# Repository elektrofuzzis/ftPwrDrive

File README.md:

# ftPwrDrive
The ftPwrDrive is a i²c based stepper motor driver for fischertechnik, Arduino &amp; Raspberry. The project contains the stepper motor drivers hardware, the firmware and interface libraries to use the hardware with multiple plattforms.

Please checkout the <a href="https://github.com/elektrofuzzis/ftPwrDrive/wiki">online manual</a>. Since the hardware is a complex smd pcb, you could buy a plug&play device at <a href="https://gundermann-software.de/shop/">gundermann.org</a>.

To check out the latest releases please follow up the <a href="https://github.com/elektrofuzzis/ftPwrDrive/wiki/Changelog">version history</a>.

<hr width="100%" />

Der ftPwrDrive ist ein Schrittmotortreiber für fischertechnik, Arduino &amp; Raspberry auf i²C-Basis. Das Projekt beinhaltet sowohl doe Schrittmotortreiberhardware und die notwendige Firmware als auch Interface Bibliotheken für unterschiedliche Plattformen.

Bitte lesen Sie das <a href="https://github.com/elektrofuzzis/ftPwrDrive/wiki">Online Manual</a>. Die Hardware besteht aus einer komplexen, SMD-bestückten Platine. Sie können den ftPwrDrive auch als fertiges Gerät bei <a href="https://gundermann-software.de/shop/">gundermann.org</a> bestellen.

Das Changelog für die aktuelle Version finden sie<a href="https://github.com/elektrofuzzis/ftPwrDrive/wiki/Changelog"> hier</a>.

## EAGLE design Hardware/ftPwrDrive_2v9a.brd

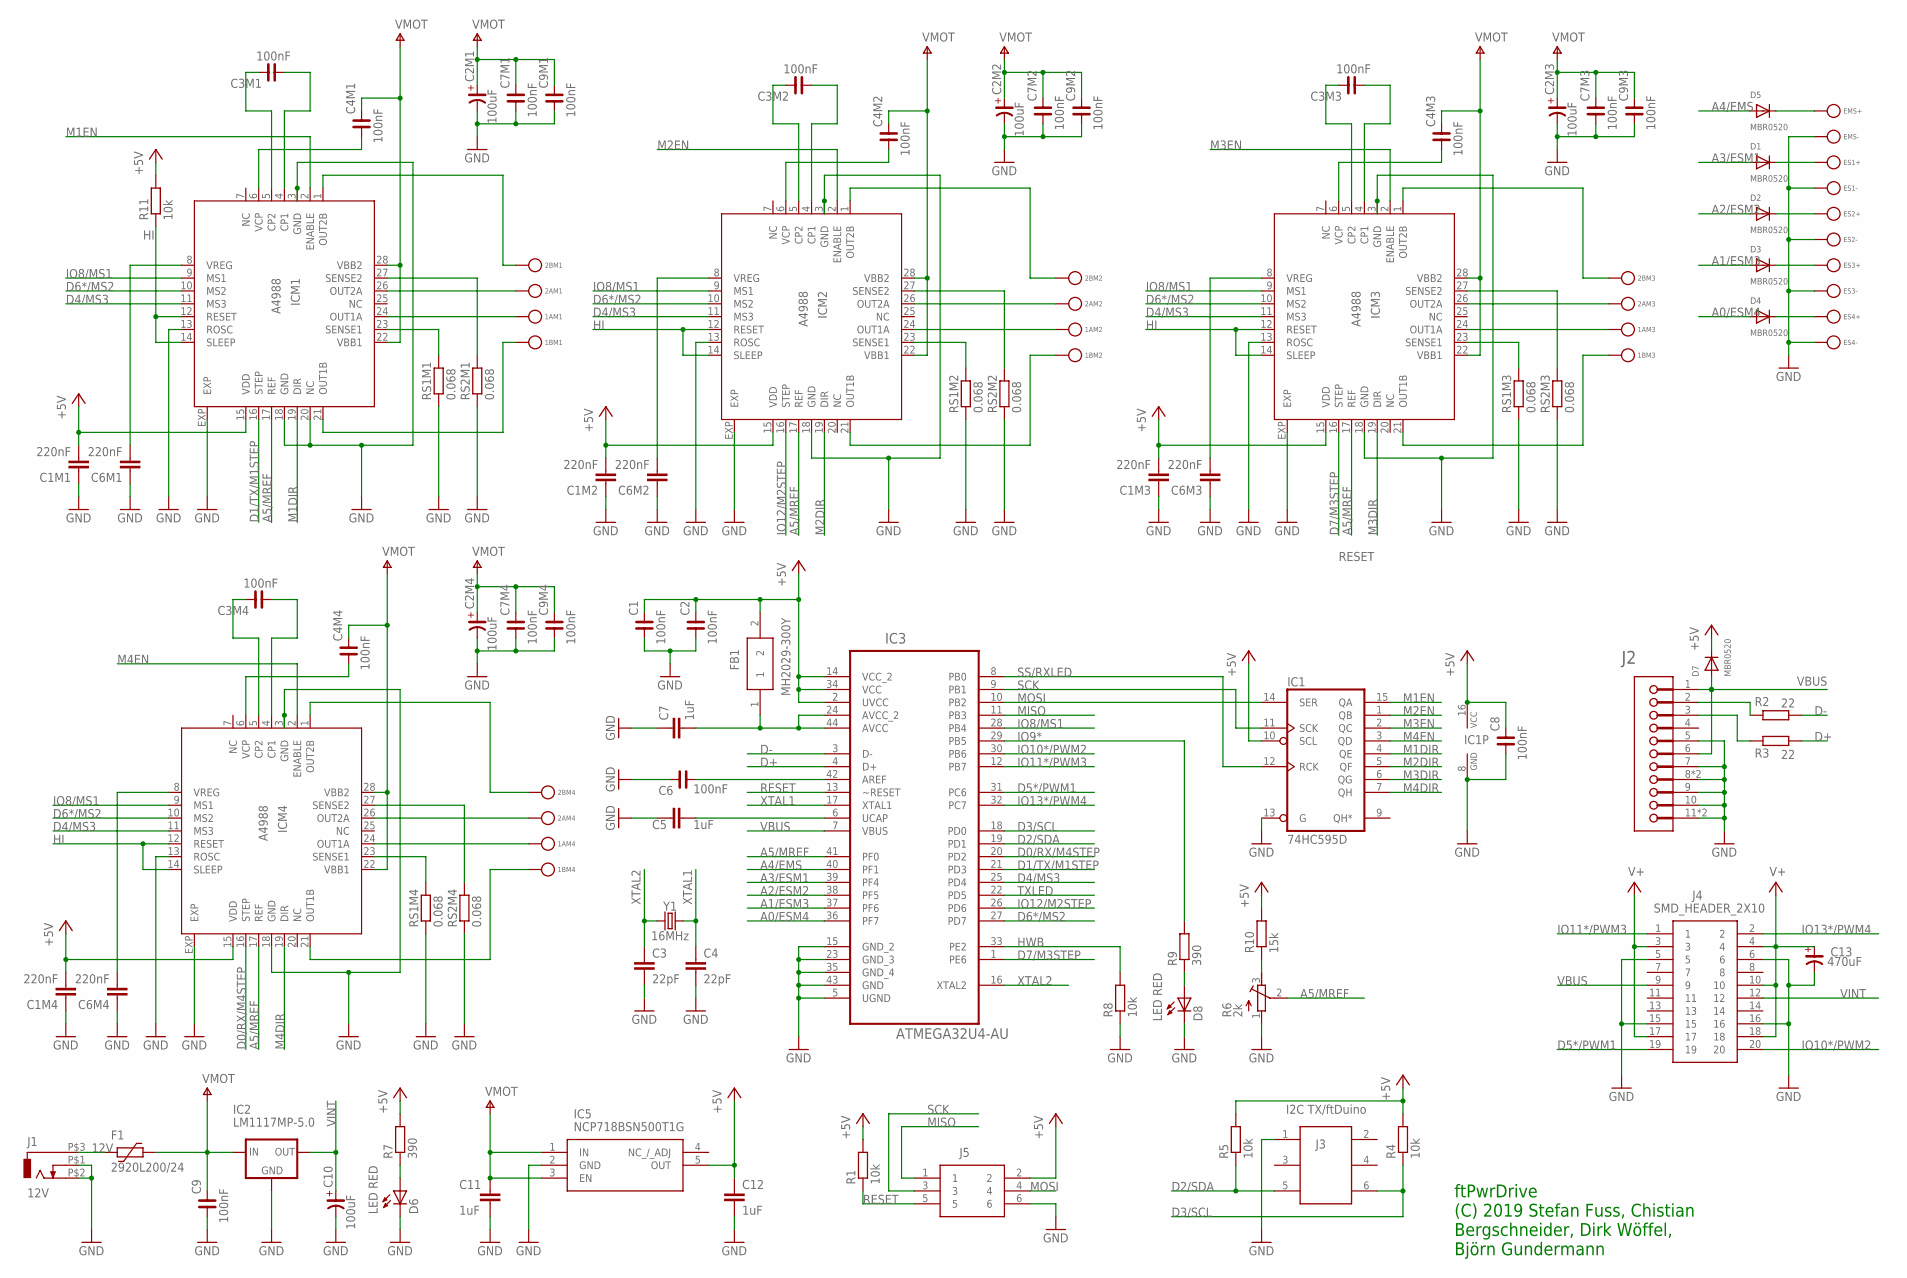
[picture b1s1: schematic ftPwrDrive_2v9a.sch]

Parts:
1AM1, 1AM2, 1AM3, 1AM4, 1BM1, 1BM2, 1BM3, 1BM4, 2AM1, 2AM2, 2AM3, 2AM4, 2BM1, 2BM2, 2BM3, 2BM4: BUNDHUELSE2; BUNDHUELSE
C1, C2, C3M1, C3M2, C3M3, C3M4, C4M1, C4M2, C4M3, C4M4, C6, C7M1, C7M2, C7M3, C7M4, C8, C9, C9M1, C9M2, C9M3, C9M4: 100nF; C0603
C1M1, C1M2, C1M3, C1M4, C6M1, C6M2, C6M3, C6M4: 220nF; C0603K
C2M1, C2M2, C2M3, C2M4, C10: 100uF; CSV-D
C3, C4: 22pF; C0603K
C5, C7, C11, C12: 1uF; C0603K
C13: 470uF; CSV-E/F
D1, D2, D3, D4, D5, D7: MBR0520; SOD-123
D6, D8: LED RED; CHIP-LED0805
EMS+: BUNDHUELSE2; BUNDHUELSE
EMS-: BUNDHUELSE2; BUNDHUELSE
ES1+, ES1-, ES2+, ES2-, ES3+, ES3-, ES4+, ES4-: BUNDHUELSE2; BUNDHUELSE
F1: 2920L200/24; 2920L
FB1: MH2029-300Y; BEADC2016X130N
IC1: 74HC595D; SO16
IC2: LM1117MP-5.0; SOT223
IC3: ATMEGA32U4-AU; QFP80P1200X1200X120-44N
IC5: NCP718BSN500T1G; SOT95P280X100-5N
ICM1, ICM2, ICM3, ICM4: A4988; QFN28ET
J1: 12V; RASM7X2
J2: AMPHENOL_10118194-0001LFAMPHENOL_10118194-0001LF_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; AMPHENOL_10118194-0001LF_0
J3: I2C TX/ftDuino; SMTHEADER06
J4: SMD_HEADER_2X10
J5: SMD_HEADER_2X03
R1, R4, R5, R8, R11: 10k; R0603
R2, R3: 22; R0603
R6: 2k; RTRIM4G/J
R7, R9: 390; R0603
R10: 15k; R0603
RS1M1, RS1M2, RS1M3, RS1M4, RS2M1, RS2M2, RS2M3, RS2M4: 0.068; R1206
Y1: 16MHz; HC49UP

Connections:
1AM1: 1AM1.P$1, ICM1.24 (OUT1A)
1AM2: 1AM2.P$1, ICM2.24 (OUT1A)
1AM3: 1AM3.P$1, ICM3.24 (OUT1A)
1AM4: 1AM4.P$1, ICM4.24 (OUT1A)
1BM1: 1BM1.P$1, ICM1.21 (OUT1B)
1BM2: 1BM2.P$1, ICM2.21 (OUT1B)
1BM3: 1BM3.P$1, ICM3.21 (OUT1B)
1BM4: 1BM4.P$1, ICM4.21 (OUT1B)
2AM1: 2AM1.P$1, ICM1.26 (OUT2A)
2AM2: 2AM2.P$1, ICM2.26 (OUT2A)
2AM3: 2AM3.P$1, ICM3.26 (OUT2A)
2AM4: 2AM4.P$1, ICM4.26 (OUT2A)
2BM1: 2BM1.P$1, ICM1.1 (OUT2B)
2BM2: 2BM2.P$1, ICM2.1 (OUT2B)
2BM3: 2BM3.P$1, ICM3.1 (OUT2B)
2BM4: 2BM4.P$1, ICM4.1 (OUT2B)
12V: F1.2, J1.P$3 (1)
+5V: C1.2, C1M1.2, C1M2.2, C1M3.2, C1M4.2, C2.2, C8.2, C12.1, D7.C, FB1.2, IC1.10 (SCL), IC1.16 (VCC), IC3.2 (UVCC), IC3.14 (VCC_2), IC3.34 (VCC), IC5.5 (OUT), ICM1.15 (VDD), ICM2.15 (VDD), ICM3.15 (VDD), ICM4.15 (VDD), J5.2, R1.2, R4.2, R5.2, R7.2, R10.2, R11.2
A0/ESM4: D4.A, IC3.36 (PF7)
A1/ESM3: D3.A, IC3.37 (PF6)
A2/ESM2: D2.A, IC3.38 (PF5)
A3/ESM1: D1.A, IC3.39 (PF4)
A4/EMS: D5.A, IC3.40 (PF1)
A5/MREF: IC3.41 (PF0), ICM1.17 (REF), ICM2.17 (REF), ICM3.17 (REF), ICM4.17 (REF), R6.2 (S)
D0/RX/M4STEP: IC3.20 (PD2), ICM4.16 (STEP)
D1/TX/M1STEP: IC3.21 (PD3), ICM1.16 (STEP)
D2/SDA: IC3.19 (PD1), J3.5, R5.1
D3/SCL: IC3.18 (PD0), J3.6, R4.1
D4/MS3: IC3.25 (PD4), ICM1.11 (MS3), ICM2.11 (MS3), ICM3.11 (MS3), ICM4.11 (MS3)
D5*/PWM1: IC3.31 (PC6), J4.19
D6*/MS2: IC3.27 (PD7), ICM1.10 (MS2), ICM2.10 (MS2), ICM3.10 (MS2), ICM4.10 (MS2)
D7/M3STEP: IC3.1 (PE6), ICM3.16 (STEP)
D+: IC3.4 (D+), R3.1
D-: IC3.3 (D-), R2.1
ES1+: D1.C, ES1+.P$1
ES1+1: D5.C, EMS+.P$1
ES2+: D2.C, ES2+.P$1
ES3+: D3.C, ES3+.P$1
ES4+: D4.C, ES4+.P$1
GND: C1.1, C1M1.1, C1M2.1, C1M3.1, C1M4.1, C2.1, C2M1.-, C2M2.-, C2M3.-, C2M4.-, C3.2, C4.2, C5.1, C6.1, C6M1.1, C6M2.1, C6M3.1, C6M4.1, C7.1, C7M1.1, C7M2.1, C7M3.1, C7M4.1, C8.1, C9.1, C9M1.1, C9M2.1, C9M3.1, C9M4.1, C10.-, C11.1, C12.2, C13.-, D6.C, D8.C, EMS-.P$1, ES1-.P$1, ES2-.P$1, ES3-.P$1, ES4-.P$1, IC1.8 (GND), IC1.13 (G), IC2.1 (GND), IC3.5 (UGND), IC3.15 (GND_2), IC3.23 (GND_3), IC3.35 (GND_4), IC3.43 (GND), IC5.2 (GND), ICM1.3 (GND), ICM1.13 (ROSC), ICM1.18 (GND), ICM1.20 (NC), ICM1.EXP, ICM2.3 (GND), ICM2.13 (ROSC), ICM2.18 (GND), ICM2.EXP, ICM3.3 (GND), ICM3.13 (ROSC), ICM3.18 (GND), ICM3.EXP, ICM4.3 (GND), ICM4.13 (ROSC), ICM4.18 (GND), ICM4.EXP, J1.P$1 (2), J1.P$2 (3), J2.5, J2.7 (MNT_2), J2.8 (MNT_3), J2.8-2 (MNT_3), J2.9 (MNT_4), J2.10 (MNT_5), J2.11 (MNT_6), J2.11-2 (MNT_6), J3.1, J4.5, J4.6, J4.15, J4.16, J5.6, R6.1 (A), R8.1, RS1M1.1, RS1M2.1, RS1M3.1, RS1M4.1, RS2M1.1, RS2M2.1, RS2M3.1, RS2M4.1
HI: ICM1.12 (RESET), ICM1.14 (SLEEP), ICM2.12 (RESET), ICM2.14 (SLEEP), ICM3.12 (RESET), ICM3.14 (SLEEP), ICM4.12 (RESET), ICM4.14 (SLEEP), R11.1
HWB: IC3.33 (PE2), R8.2
IO8/MS1: IC3.28 (PB4), ICM1.9 (MS1), ICM2.9 (MS1), ICM3.9 (MS1), ICM4.9 (MS1)
IO9*: IC3.29 (PB5), R9.2
IO10*/PWM2: IC3.30 (PB6), J4.20
IO11*/PWM3: IC3.12 (PB7), J4.1
IO12/M2STEP: IC3.26 (PD6), ICM2.16 (STEP)
IO13*/PWM4: IC3.32 (PC7), J4.2
M1DIR: IC1.4 (QE), ICM1.19 (DIR)
M1EN: IC1.15 (QA), ICM1.2 (ENABLE)
M2DIR: IC1.5 (QF), ICM2.19 (DIR)
M2EN: IC1.1 (QB), ICM2.2 (ENABLE)
M3DIR: IC1.6 (QG), ICM3.19 (DIR)
M3EN: IC1.2 (QC), ICM3.2 (ENABLE)
M4DIR: IC1.7 (QH), ICM4.19 (DIR)
M4EN: IC1.3 (QD), ICM4.2 (ENABLE)
MISO: IC3.11 (PB3), J5.1
MOSI: IC1.14 (SER), IC3.10 (PB2), J5.4
unnamed: J2.2, R2.2
unnamed: J2.3, R3.2
unnamed: D8.A, R9.1
unnamed: R6.3 (E), R10.1
unnamed: C5.2, IC3.6 (UCAP)
unnamed: C7.2, FB1.1, IC3.24 (AVCC_2), IC3.44 (AVCC)
unnamed: C6.2, IC3.42 (AREF)
unnamed: D6.A, R7.1
RESET: IC3.13 (~RESET), J5.5, R1.1
SCK: IC1.11 (SCK), IC3.9 (PB1), J5.3
SS/RXLED: IC1.12 (RCK), IC3.8 (PB0)
TXLED: IC3.22 (PD5)
V+: C13.+, J4.3, J4.4, J4.10, J4.17, J4.18
VBUS: D7.A, IC3.7 (VBUS), J2.1, J2.6 (MNT_1), J4.9
VINT: C10.+, IC2.2 (OUT), IC2.4 (OUT), J4.12
VMOT: C2M1.+, C2M2.+, C2M3.+, C2M4.+, C4M1.2, C4M2.2, C4M3.2, C4M4.2, C7M1.2, C7M2.2, C7M3.2, C7M4.2, C9.2, C9M1.2, C9M2.2, C9M3.2, C9M4.2, C11.2, F1.1, IC2.3 (IN), IC5.1 (IN), IC5.3 (EN), ICM1.22 (VBB1), ICM1.28 (VBB2), ICM2.22 (VBB1), ICM2.28 (VBB2), ICM3.22 (VBB1), ICM3.28 (VBB2), ICM4.22 (VBB1), ICM4.28 (VBB2)
XCP1: C3M1.1, ICM1.4 (CP1)
XCP2: C3M1.2, ICM1.5 (CP2)
XCP5: C3M2.1, ICM2.4 (CP1)
XCP6: C3M2.2, ICM2.5 (CP2)
XCP7: C3M3.1, ICM3.4 (CP1)
XCP8: C3M3.2, ICM3.5 (CP2)
XCP9: C3M4.1, ICM4.4 (CP1)
XCP10: C3M4.2, ICM4.5 (CP2)
XSENSE1: ICM1.23 (SENSE1), RS1M1.2
XSENSE2: ICM1.27 (SENSE2), RS2M1.2
XSENSE5: ICM2.27 (SENSE2), RS2M2.2
XSENSE6: ICM2.23 (SENSE1), RS1M2.2
XSENSE7: ICM3.27 (SENSE2), RS2M3.2
XSENSE8: ICM3.23 (SENSE1), RS1M3.2
XSENSE9: ICM4.27 (SENSE2), RS2M4.2
XSENSE10: ICM4.23 (SENSE1), RS1M4.2
XTAL1: C4.1, IC3.17 (XTAL1), Y1.2
XTAL2: C3.1, IC3.16 (XTAL2), Y1.1
XVCP: C4M1.1, ICM1.6 (VCP)
XVCP2: C4M2.1, ICM2.6 (VCP)
XVCP3: C4M3.1, ICM3.6 (VCP)
XVCP4: C4M4.1, ICM4.6 (VCP)
XVREG: C6M1.2, ICM1.8 (VREG)
XVREG2: C6M2.2, ICM2.8 (VREG)
XVREG3: C6M3.2, ICM3.8 (VREG)
XVREG4: C6M4.2, ICM4.8 (VREG)

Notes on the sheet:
ftPwrDrive (C) 2019 Stefan Fuss, Chistian Bergschneider, Dirk Wöffel, Björn Gundermann

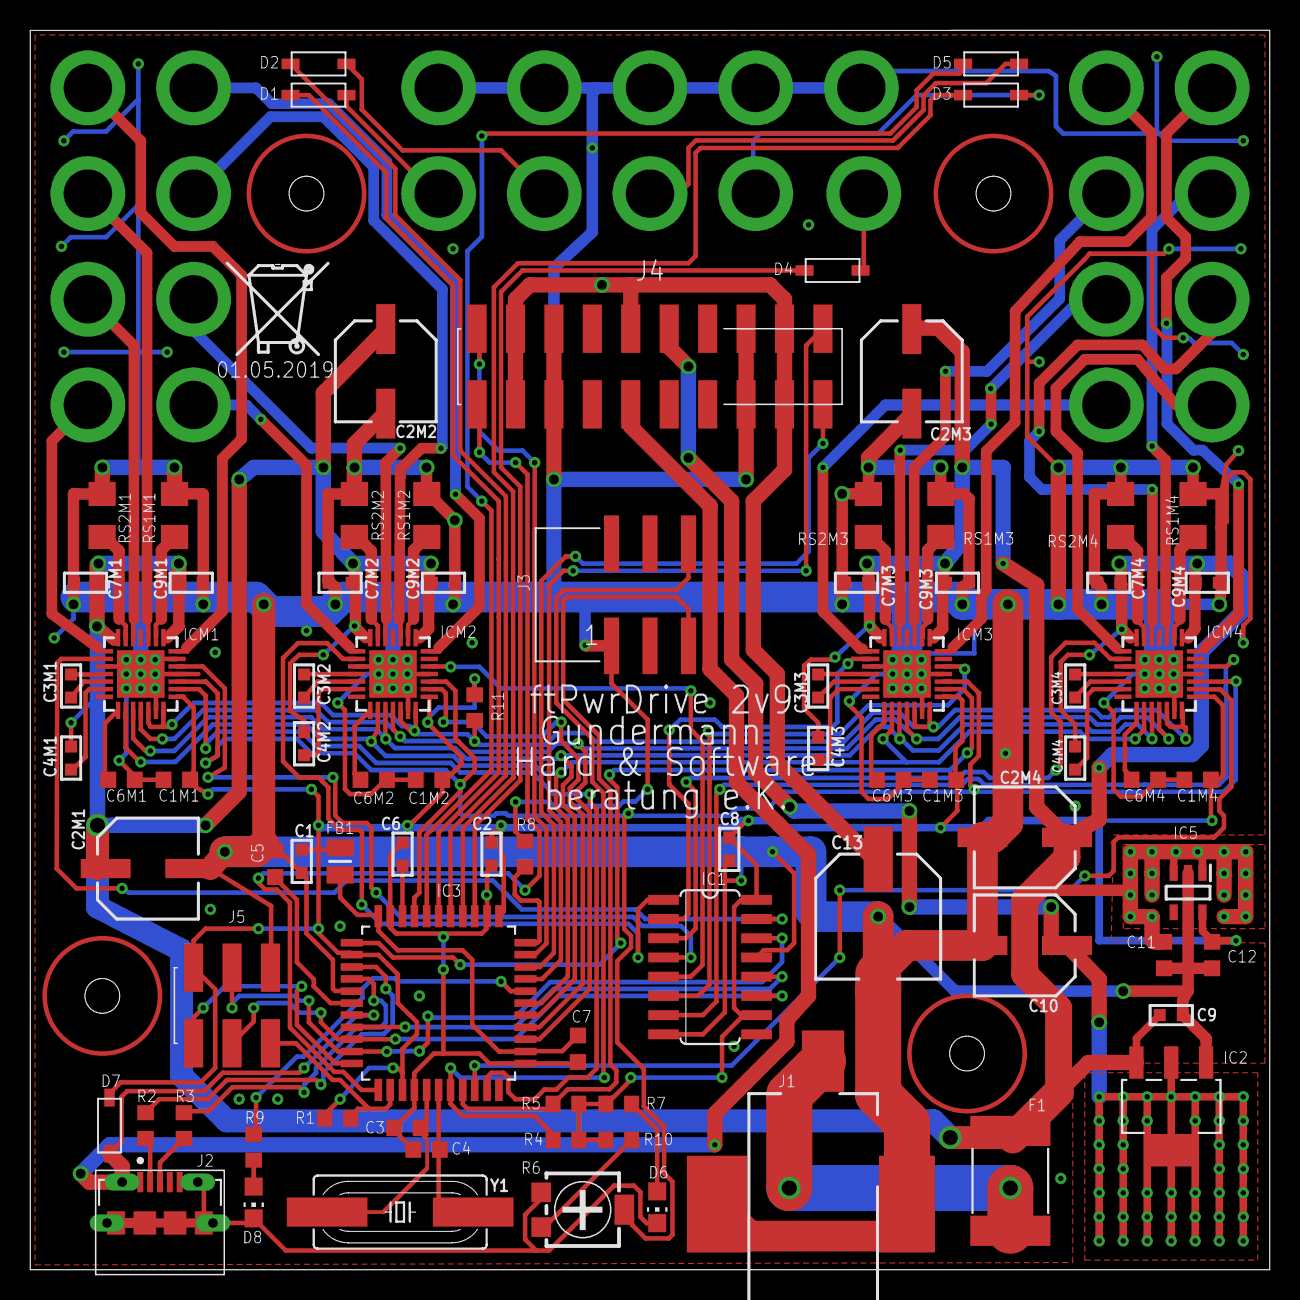
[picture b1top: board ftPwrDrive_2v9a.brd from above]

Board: 2 copper layers, 81.9 x 81.9 mm, 111 parts (0 on the bottom side), 99 nets.

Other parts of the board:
U$9: ROHS_BIN

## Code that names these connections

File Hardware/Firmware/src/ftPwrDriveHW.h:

#ifndef ftPwrDriveHW_h
#define ftPwrDriveHW_h

// Hardware defintions for ftPwrDrive
//
// 13.04.19 / V1.00
//
// (C) 2019 Christian Bergschneider & Stefan Fuss

#define MS1    8  // D8
#define MS2    6  // D6
#define MS3    4  // D4

#define MREFI  A5 // A5

#define SERVO1 13 // D13
#define SERVO2 11 // D11
#define SERVO3 10 // D10
#define SERVO4 5  // D5

#define M1STEP 1  // D1
#define M2STEP 12 // D12
#define M3STEP 7  // D7
#define M4STEP 0  // D0

#define ES1    A3  // A3
#define ES2    A2  // A2
#define ES3    A1  // A1
#define ES4    A0  // A0
#define EMS    A4  // A4

#define LED    9   // D9

#define M1EN   0   // QA
#define M2EN   1   // QB
#define M3EN   2   // QC
#define M4EN   3   // QD

#define M1DIR  4   // QE
#define M2DIR  5   // QF
#define M3DIR  6   // QG
#define M4DIR  7   // QH

#define MaxServo   4
#define MaxStepper 4

const int ENABLE[MaxStepper]    = { M1EN, M2EN, M3EN, M4EN };
const int DIRECTION[MaxStepper] = { M1DIR, M2DIR, M3DIR, M4DIR };
const int STEP[MaxStepper]      = { M1STEP, M2STEP, M3STEP, M4STEP };
const int ES[MaxStepper]        = { ES1, ES2, ES3, ES4 };
const int SERVO[MaxServo]       = { SERVO1, SERVO2, SERVO3, SERVO4 };

#endif

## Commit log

2019-08-30 initial version 0.9
2019-08-31 hex firmware added
2019-09-05 FW V0.91 - servo support
2019-09-17 Add files via upload
    Initiale Version des Handbuches mit Beschreibung für die Firmware V0.92
2019-09-20 new Version 0.93
2019-09-26 missing ftPwrDriveHW.h added
2019-12-25 ROBOPro library
    initial version of ROBOPro library.
    Works with Firmware 0.93.
2019-12-25 working on wiki
2019-12-25 correct some typos
2019-12-31 Version 0.94
    - Use with firmware 0.94 or higher
    - bugfix watchdog (firmware)
    - constants without FTPWRDRIVE, e.g. M1 instead of FTPWRDRIVE_M1
    - new funtions setGearFactor, setRelDistanceR, setAbsDistanceR
2020-01-02 wiki
2020-01-11 new files for wiki
2020-01-19 Added Python library
    Added the .py and .pyc file of the python library
2020-12-12 Integrated Python Lib
2020-12-12 Removed old ver
2021-04-01 Fixed typo
2022-02-08 Update for HW V3
2022-02-10 Version 0.99

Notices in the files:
parts and their libraries:
rc-master-smd: Copyright (C) 2007, Bob Starr
SparkFun-Clocks: Licensing: Creative Commons ShareAlike 4.0 International - https://creativecommons.org/licenses/by-sa/4.0
